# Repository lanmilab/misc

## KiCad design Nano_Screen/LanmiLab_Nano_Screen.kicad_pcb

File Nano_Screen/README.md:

LanmiLab Nano Screen
User Interface Board,
Nano Shield for 0.91" Display

PCB

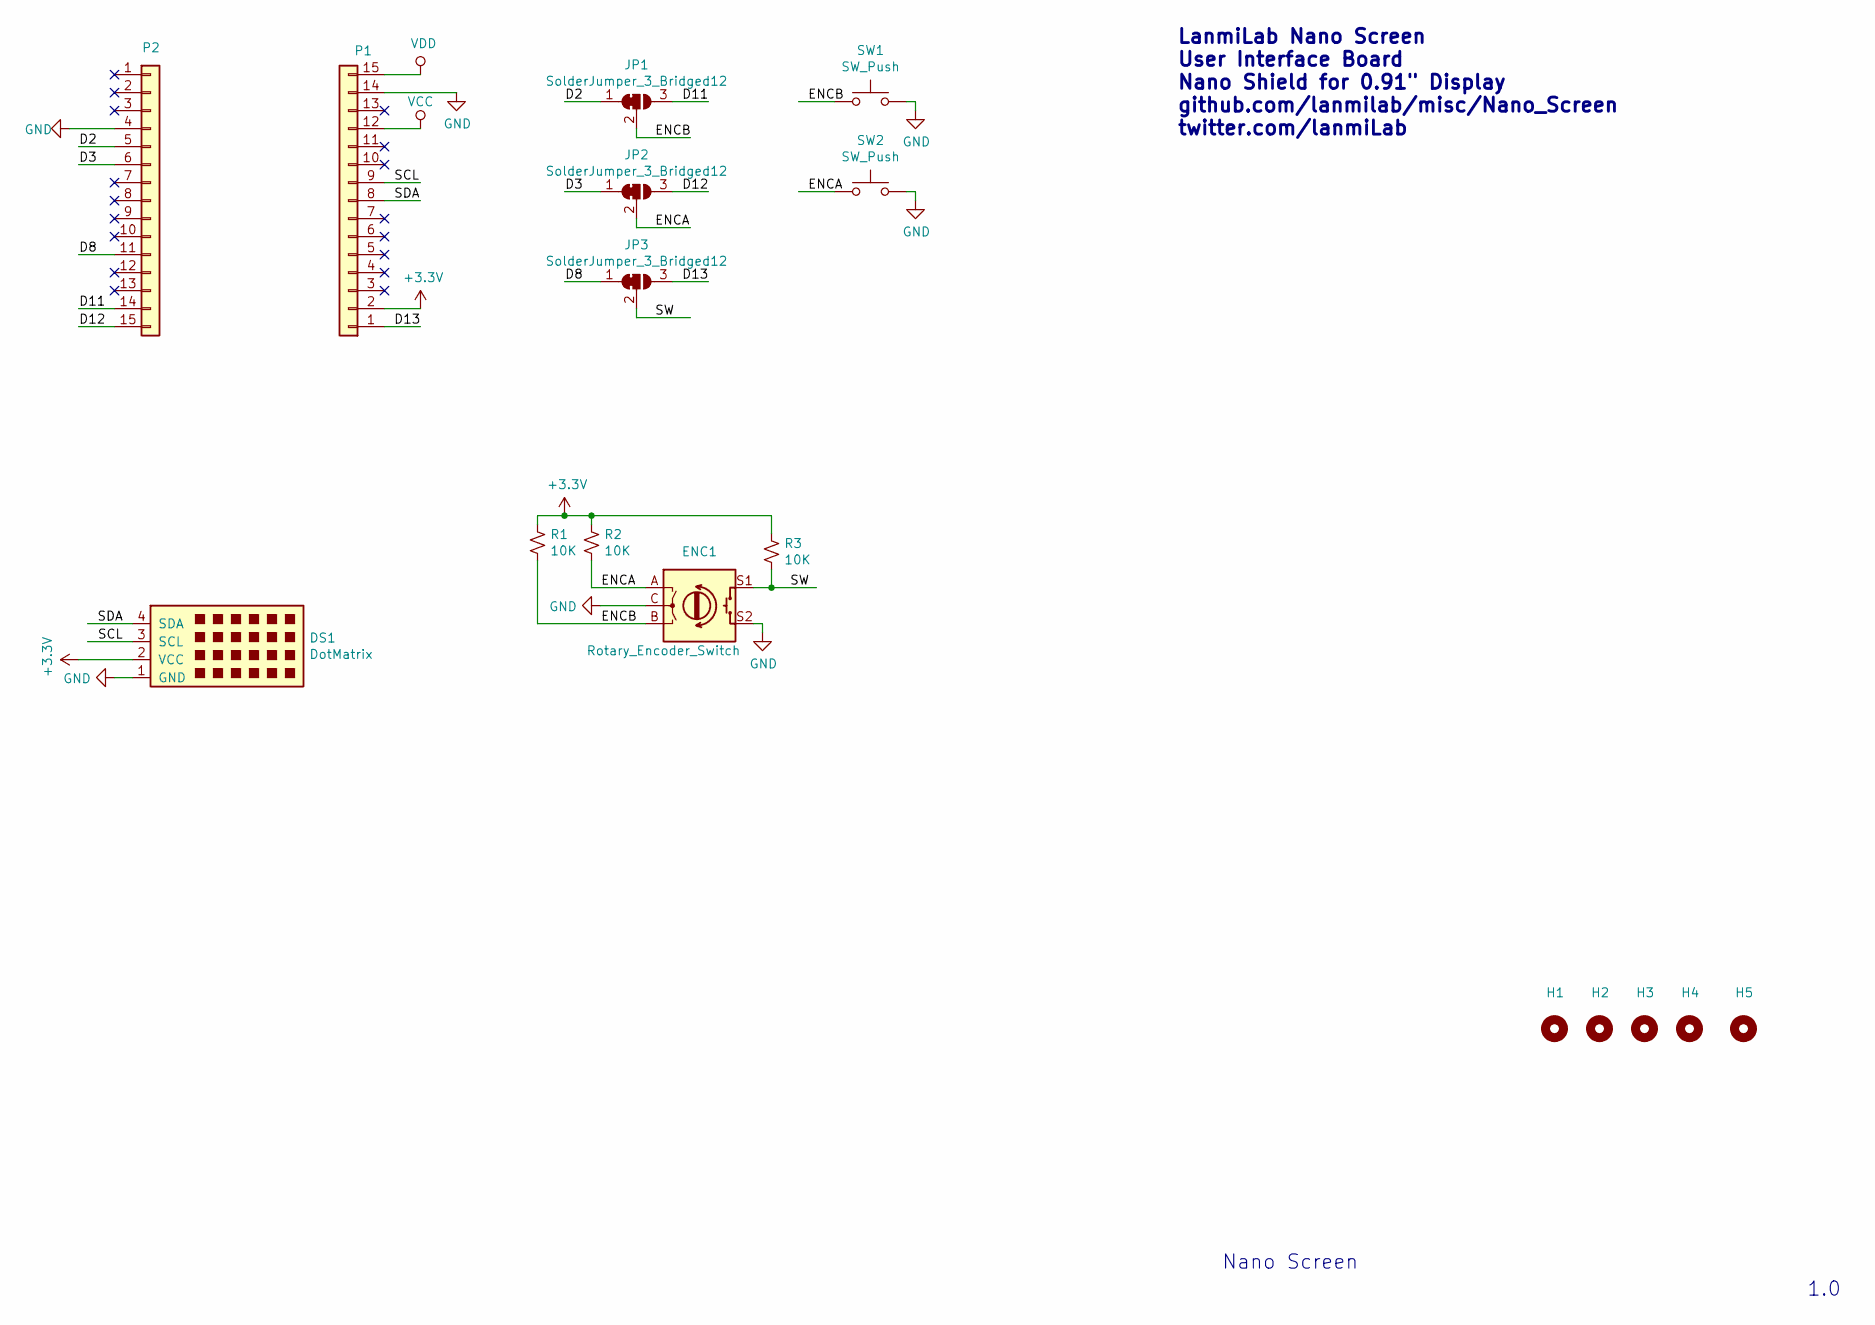
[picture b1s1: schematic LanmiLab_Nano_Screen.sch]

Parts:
DS1: DotMatrix; 091_OLED_DISPLAY; Part Number REA012832F
ENC1: Rotary_Encoder_Switch; RotaryEncoder_Alps_EC11E-Switch_Vertical_H20mm; Part Number EC11E18244A5
H1, H2, H3, H4: MountingHole_Pad; MountingHole_2.1mm
H5: MountingHole_Pad; MountingHole_2.7mm_M2.5
JP1, JP2, JP3: SolderJumper_3_Bridged12; SolderJumper-3_P1.3mm_Bridged12_RoundedPad1.0x1.5mm_NumberL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
P1, P2: Conn_01x15; PinSocket_1x15_P2.54mm_Vertical; Part Number PPPC151LFBN-RC
R1, R2, R3: 10K; R_Axial_DIN0204_L3.6mm_D1.6mm_P5.08mm_Horizontal; Part Number CFR16J10K
SW1, SW2: SW_Push; SW_PUSH_6mm; Part Number B3F6052

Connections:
+3V3: DS1.2 (VCC), P1.2, R1.1, R2.1, R3.1
/D2: JP1.1 (A), P2.5
/D3: JP2.1 (A), P2.6
/D8: JP3.1 (A), P2.11
/D11: JP1.3 (B), P2.14
/D12: JP2.3 (B), P2.15
/D13: JP3.3 (B), P1.1
/ENCA: ENC1.A, JP2.2 (C), R2.2, SW2.1
/ENCB: ENC1.B, JP1.2 (C), R1.2, SW1.1
/SCL: DS1.3 (SCL), P1.9
/SDA: DS1.4 (SDA), P1.8
/SW: ENC1.S1, JP3.2 (C), R3.2
GND: DS1.1 (GND), ENC1.C, ENC1.MP, ENC1.S2, P1.14, P2.4, SW1.2, SW2.2
VCC: P1.12
VDD: P1.15

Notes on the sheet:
Nano Screen
LanmiLab Nano Screen User Interface Board Nano Shield for 0.91" Display github.com/lanmilab/misc/Nano_Screen twitter.com/lanmiLab
1.0

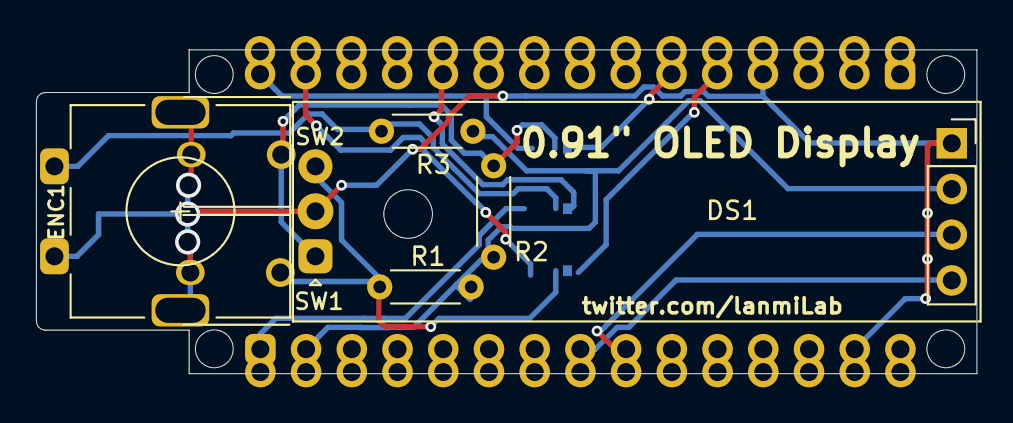
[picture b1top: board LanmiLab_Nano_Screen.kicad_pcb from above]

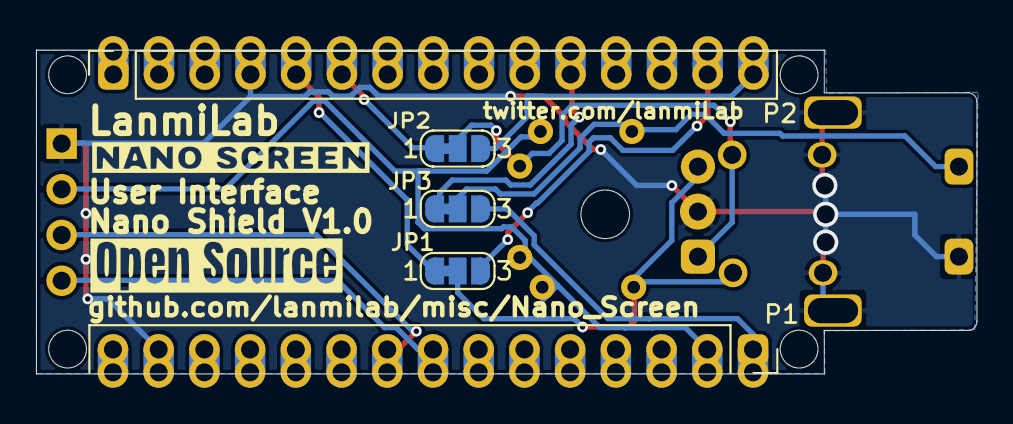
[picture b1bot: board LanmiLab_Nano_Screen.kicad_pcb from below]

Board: 2 copper layers, 52.2 x 18.0 mm, 17 parts (5 on the bottom side), 13 nets.

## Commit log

2020-05-07 KiCad Design Files upload
2020-05-07 Gerbers and BOM upload
2020-05-07 Image links update
2020-05-07 Demo code
